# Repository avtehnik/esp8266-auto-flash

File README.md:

# esp8266 auto flash tool
https://youtu.be/RyvSWPqZMKo

If you have serial port with cp2102 ic looks like this

You can make this simple pcb to make flashing esp8266 more easily

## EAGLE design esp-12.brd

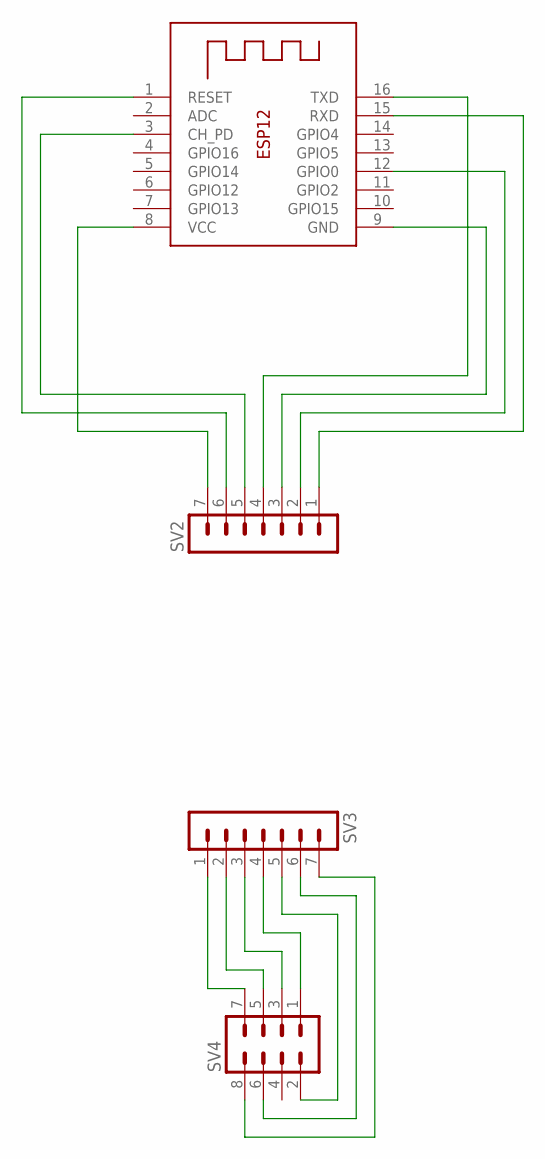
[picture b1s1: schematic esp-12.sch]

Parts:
SV2, SV3: MA07-1
SV4: MA04-2
X1: ESP-12

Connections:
unnamed: SV2.7, X1.8 (VCC)
unnamed: SV2.3, X1.9 (GND)
unnamed: SV2.5, X1.3 (CH_PD)
unnamed: SV2.6, X1.1 (RESET)
unnamed: SV2.4, X1.16 (TXD)
unnamed: SV2.1, X1.15 (RXD)
unnamed: SV2.2, X1.12 (GPIO0)
unnamed: SV3.1, SV4.7
unnamed: SV3.2, SV4.5
unnamed: SV3.3, SV4.3
unnamed: SV3.4, SV4.1
unnamed: SV3.5, SV4.2
unnamed: SV3.6, SV4.6
unnamed: SV3.7, SV4.8

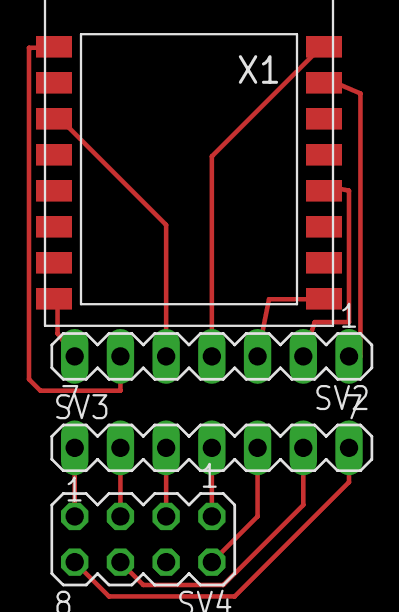
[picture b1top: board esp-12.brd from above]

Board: 2 copper layers, 4 parts (0 on the bottom side), 14 nets.

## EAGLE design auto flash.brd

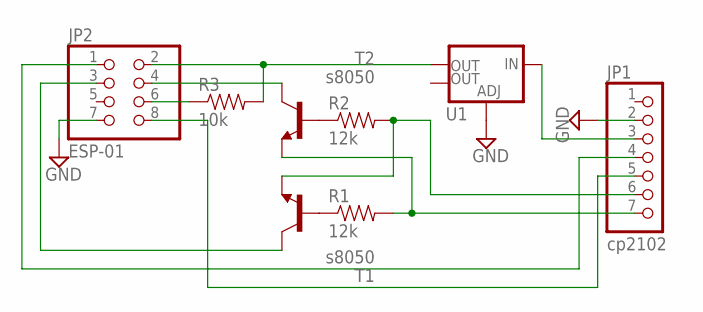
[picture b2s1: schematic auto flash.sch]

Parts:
JP1: cp2102; 1X07/90
JP2: ESP-01; 2X04
R1, R2: 12k; 0805
R3: 10k; 0805
T1, T2: s8050; TO92-EBC-OVAL
U1: V_REG_LM1117SOT223; SOT223

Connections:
ESP-01: JP1.4, JP2.1
GND: JP1.2, JP2.7, U1.1 (ADJ)
unnamed: JP1.7, R1.2, T2.E
unnamed: R1.1, T1.B
unnamed: R2.1, T2.B
unnamed: JP2.4, T2.C
unnamed: JP1.6, R2.2, T1.E
unnamed: JP2.3, T1.C
unnamed: JP1.5, JP2.8
unnamed: JP2.2, R3.2, U1.2 (OUT)
unnamed: JP1.3, U1.3 (IN)
unnamed: JP2.6, R3.1

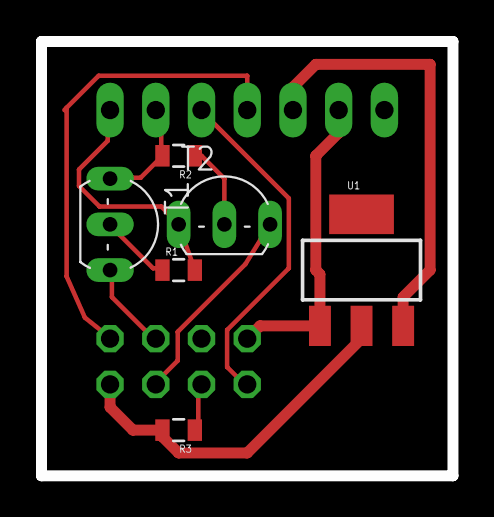
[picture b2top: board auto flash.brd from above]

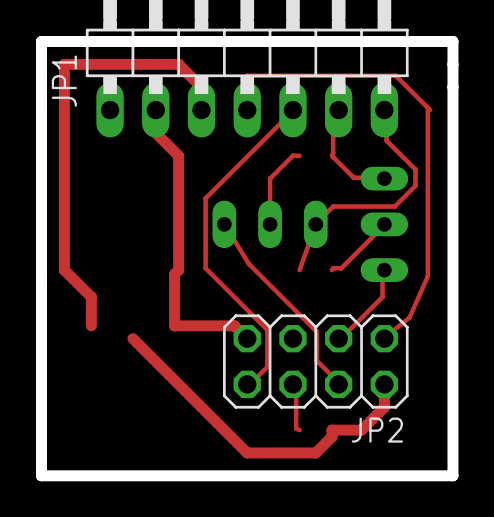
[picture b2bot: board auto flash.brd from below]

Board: 2 copper layers, 22.9 x 24.1 mm, 8 parts (2 on the bottom side), 12 nets.

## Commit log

2016-02-06 add files
2016-02-06 add serial port image
2016-02-06 update image
2016-02-07 add photos
2016-02-08 add esp-12, esp-07 adapter

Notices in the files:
parts and their libraries:
SparkFun-Resistors: Licensing: Creative Commons ShareAlike 4.0 International - https://creativecommons.org/licenses/by-sa/4.0
